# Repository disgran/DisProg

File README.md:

# DisProg™

DisProg™ es una placa de adaptador USB a serie que se fundamenta en el popular chip CP2102N, incluyendo un circuito de restablecimiento automático ESP32. A diferencia de los módulos económicos que puedes encontrar en Aliexpress, este adaptador destaca por su confiabilidad y versatilidad simultánea. Su confiabilidad se deriva del uso de un conocido chip de adaptador USB a serie proveniente de un proveedor reconocido, y su versatilidad radica en la inclusión del circuito de restablecimiento automático ESP32 IO & EN, eliminando la necesidad de implementarlo en la placa de destino.

Otro punto a favor de DisProg™ es su regulador de voltaje integrado de 3.3V y 500mA, capaz de alimentar el dispositivo que estás programando. Como opción adicional, puedes conectar un cable JST personalizado que facilita la programación segura de relés Shelly sin depender de la alimentación principal. Esto sitúa a DisProg™ como uno de los mejores adaptadores USB/serie para cargar el firmware de tus dispositivos con Tasmota o ESPHome.

Para obtener más detalles sobre este proyecto, te invito a consultar la entrada correspondiente en https://disgran.com/disprog.

Si estás interesado en adquirir uno de estos adaptadores preensamblados, te invito a visitar mi tienda en https://disgran.com

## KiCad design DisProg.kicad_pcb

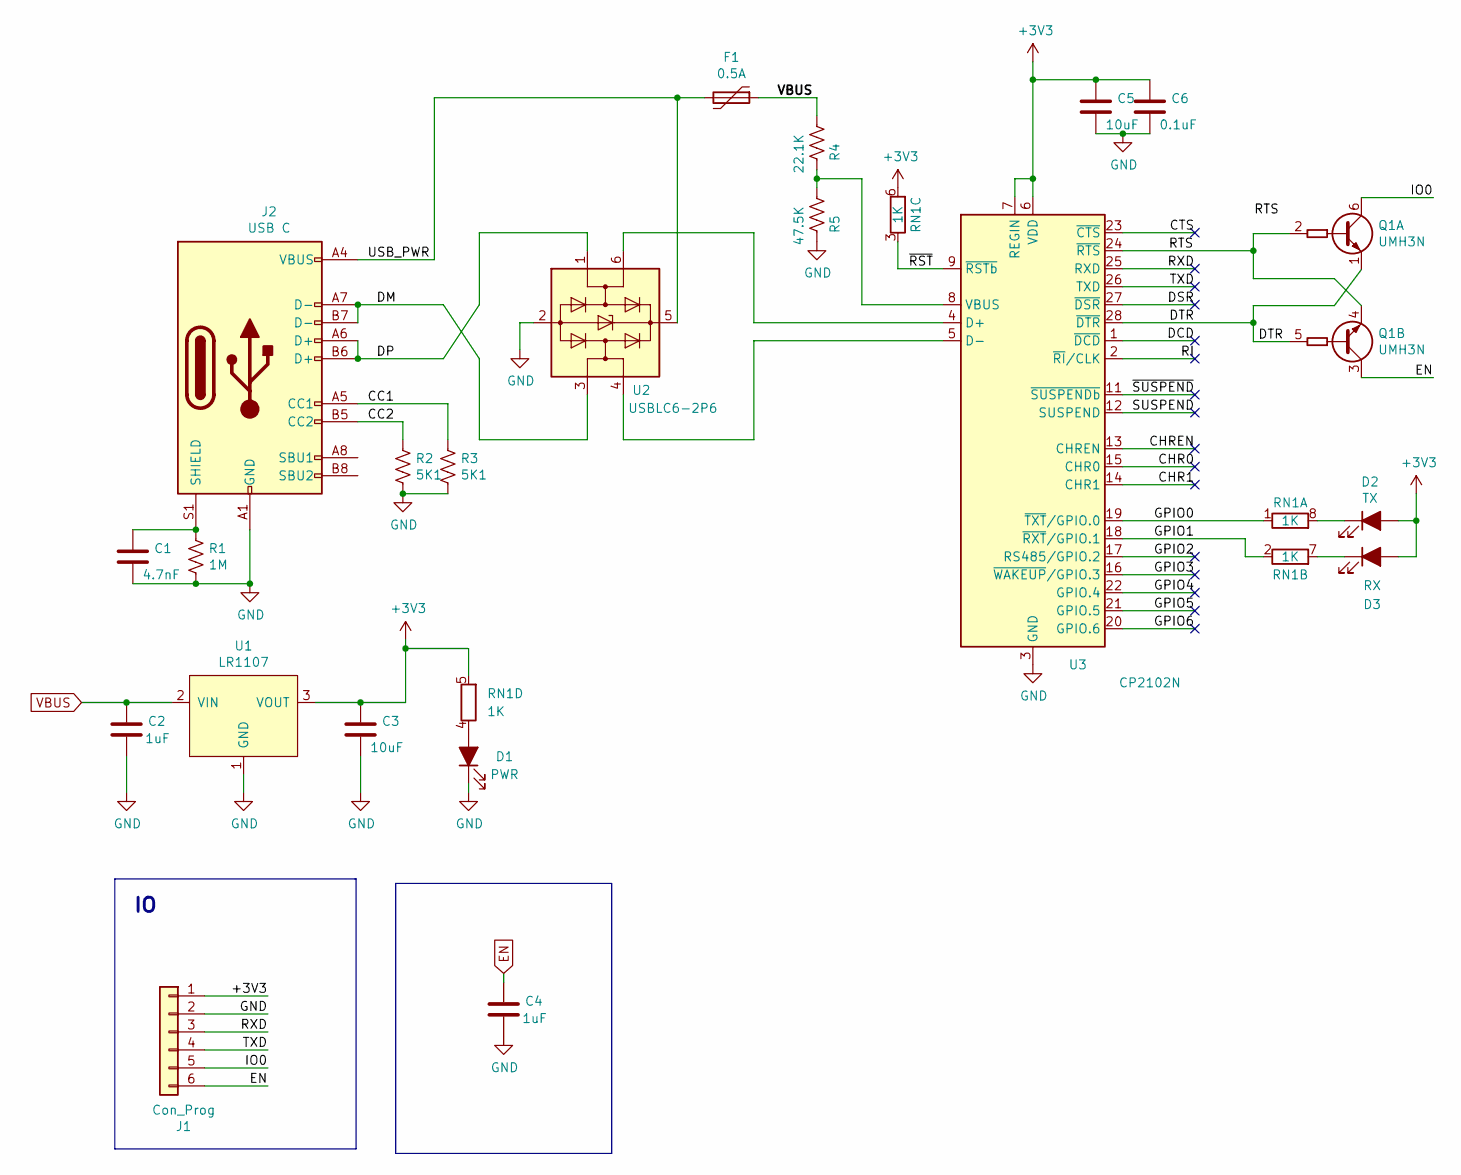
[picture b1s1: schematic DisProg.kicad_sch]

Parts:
C1: 4.7nF; C_0805_2012Metric; Voltage 50V; LCSC C53987
C2: 1uF; C_0603_1608Metric; LCSC C15849
C3: 10uF; C_0603_1608Metric; LCSC C96446
C4: 1uF; C_0603_1608Metric
C5: 10uF; C_0603_1608Metric; LCSC C19702
C6: 0.1uF; C_0603_1608Metric; LCSC C14663
D1: PWR; LED_0603_1608Metric; LCSC C2286
D2: TX; LED_0603_1608Metric; LCSC C72043
D3: RX; LED_0603_1608Metric; LCSC C2286
F1: 0.5A; Fuse_0603_1608Metric; LCSC C207014
J1: Con_Prog; JST_SM06B-SRSS-TB_LF__SN_; LCSC C160405
J2: USB C; USB_C_Receptacle_HRO_TYPE-C-31-M-12; LCSC C165948
Q1: UMH3N; SOT-363_SC-70-6; LCSC C62892
R1: 1M; R_0603_1608Metric; LCSC C2090547
R2, R3: 5K1; R_0603_1608Metric
R4: 22.1K; R_0603_1608Metric
R5: 47.5K; R_0603_1608Metric
RN1: 1K; R_Array_Convex_4x0603
U1: LR1107; SOT-89-3; LCSC C171498
U2: USBLC6-2P6; SOT-666
U3: CP2102N; QFN-28-1EP_5x5mm_P0.5mm_EP3.35x3.35mm; LCSC C964632

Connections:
+3V3: C3.1, C5.1, C6.1, D2.2 (A), D3.2 (A), J1.1, RN1.5 (R4.2), RN1.6 (R3.2), U1.3 (VOUT), U3.6 (VDD), U3.7 (REGIN)
/CC1: J2.A5 (CC1), R3.1
/CC2: J2.B5 (CC2), R2.1
/CHR0: U3.15 (CHR0)
/CHR1: U3.14 (CHR1)
/CHREN: U3.13 (CHREN)
/CTS: U3.23 (~CTS)
/DCD: U3.1 (~DCD)
/DM: J2.A7 (D-), J2.B7 (D-), U2.3 (I/O2)
/DP: J2.A6 (D+), J2.B6 (D+), U2.1 (I/O1)
/DSR: U3.27 (~DSR)
/DTR: Q1.1 (E1), Q1.5 (B2), U3.28 (~DTR)
/GPIO0: RN1.1 (R1.1), U3.19 (~TXT/GPIO.0)
/GPIO1: RN1.2 (R2.1), U3.18 (~RXT/GPIO.1)
/GPIO2: U3.17 (RS485/GPIO.2)
/GPIO3: U3.16 (~WAKEUP/GPIO.3)
/GPIO4: U3.22 (GPIO.4)
/GPIO5: U3.21 (GPIO.5)
/GPIO6: U3.20 (GPIO.6)
/IO0: J1.5, Q1.6 (C1)
/RI: U3.2 (~RI/CLK)
/RTS: Q1.2 (B1), Q1.4 (E2), U3.24 (~RTS)
/RXD: J1.3, U3.25 (RXD)
/SUSPEND: U3.12 (SUSPEND)
/TXD: J1.4, U3.26 (TXD)
/USB_PWR: F1.2, J2.A4 (VBUS), J2.A9 (VBUS), J2.B4 (VBUS), J2.B9 (VBUS), U2.5 (VBUS)
/~RST: RN1.3 (R3.1), U3.9 (~RSTb)
/~SUSPEND: U3.11 (~SUSPENDb)
EN: C4.1, J1.6, Q1.3 (C2)
GND: C1.2, C2.2, C3.2, C4.2, C5.2, C6.2, D1.1 (K), J1.2, J2.A1 (GND), J2.A12 (GND), J2.B1 (GND), J2.B12 (GND), R1.2, R2.2, R3.2, R5.2, U1.1 (GND), U2.2 (GND), U3.3 (GND), U3.29 (GND)
unnamed: D1.2 (A), RN1.4 (R4.1)
unnamed: D2.1 (K), RN1.8 (R1.2)
unnamed: D3.1 (K), RN1.7 (R2.2)
unnamed: C1.1, J2.S1 (SHIELD), R1.1
unnamed: U2.6 (I/O1), U3.4 (D+)
unnamed: U2.4 (I/O2), U3.5 (D-)
unnamed: R4.2, R5.1, U3.8 (VBUS)
VBUS: C2.1, F1.1, R4.1, U1.2 (VIN)

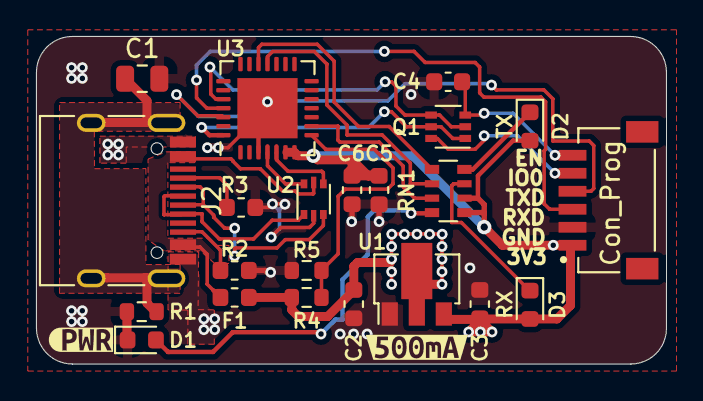
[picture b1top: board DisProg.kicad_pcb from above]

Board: 2 copper layers, 35.0 x 18.2 mm, 24 parts (0 on the bottom side), 24 nets.

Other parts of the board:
kibuzzard-62357631: G***; kibuzzard-62357631
kibuzzard-62357776: G***; kibuzzard-62357776

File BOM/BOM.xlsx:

Qty | Reference(s) | Value | Footprint | Datasheet | LCSC | PN
1 | C1 | 4.7nF | Capacitor_SMD:C_1206_3216Metric |  | C107198 | CC1206KKX7RCBB472
2 | C2, C4 | 1uF | Capacitor_SMD:C_0603_1608Metric |  | C1592 | CL10A105KO8NNNC
2 | C3, C5 | 10uF | Capacitor_SMD:C_0603_1608Metric |  | C92487 | CL10A106MO8NQNC
1 | C6 | 0.1uF | Capacitor_SMD:C_0603_1608Metric |  | C24452 | CL10B104JB8NNNC
1 | D1 | PWR | LED_SMD:LED_0603_1608Metric |  | C193902 | NCD0603R5
1 | D2 | TX | LED_SMD:LED_0603_1608Metric |  | C84267 | NCD0603G1
1 | D3 | RX | LED_SMD:LED_0603_1608Metric |  | C193902 | NCD0603R5
1 | F1 | 0.5A | Fuse:Fuse_0603_1608Metric |  | C207014 | 0603L050SLYR
1 | J1 | Link | JST_SH_BM06B-SRSS-TB_1x06-1MP_P1.00mm_Horz. |  | C145963 | BOOMELE
1 | J3 | USB_C | TYPE-C-31-M-12 |  | C165948 | TYPE-C-31-M-12
1 | Q1 | UMH3N | Package_TO_SOT_SMD:SOT-363_SC-70-6 |  | C62892 | UMH3N
1 | R1 | 1M | Resistor_SMD:R_1206_3216Metric |  | C17927 | 1206W4F1004T5E
2 | R2, R3 | 5K1 | Resistor_SMD:R_0603_1608Metric |  | C23186 | 0603WAF5101T5E
1 | R4 | 22.1K | Resistor_SMD:R_0603_1608Metric |  | C25961 | 0603WAF2212T5E
1 | R5 | 47.5K | Resistor_SMD:R_0603_1608Metric |  | C23061 | 0603WAF4752T5E
1 | RN1 | 1K | Resistor_SMD:R_Array_Convex_4x0603 |  | C425239 | 4D03WGF1001T5E
1 | U1 | LR1107 | Package_TO_SOT_SMD:SOT-89-3 |  | C171498 | LR1107G-33-AB3-C-R
1 | U2 | USBLC6-2P6 | Package_TO_SOT_SMD:SOT-666 |  | C2827693 | USBLC6-2P6
1 | U3 | CP2102N | Package_DFN_QFN:QFN-28-1EP_5x5mm_P0.5mm_EP3.35x3.35mm |  | C964632 | CP2102N-A02-GQFN28R

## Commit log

2023-12-31 Rename PCB.png to Disprog.png
2023-12-31 Rename Disprog.png to DisProg.png
